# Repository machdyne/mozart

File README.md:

# Mozart Motherboard

Mozart is a motherboard that when paired with a [Sechzig](https://github.com/machdyne/sechzig) compute module can function as a computer.

This repo contains schematics, PCB layouts, pinouts and documentation.

Find more information on the [Mozart product page](https://machdyne.com/product/mozart-motherboard/).

## Using Mozart

Mozart requires a Sechzig module to power on. **When inserting a Sechzig module, make sure that pin 2 on Mozart and pin 2 on the module are both on the same side.**

## Firmware

Mozart has a JTAG and USB CDC interface that are both accessible on the USB-C port. These interfaces are provided by a [fork of pico-dirtyJtag](https://github.com/machdyne/mozart/tree/main/firmware). You can update the RP2040 firmware by holding down the BOOT button and then applying power.

To build the firmware from source:

```
$ cd firmware/pico-dirtyJtag
$ mkdir build
# if your Mozart has Zetta flash:
$ cmake ..
# or if your Mozart has Adesto flash:
$ cmake .. -DPICO_DEFAULT_BOOT_STAGE2_FILE=/your-pico-sdk-directory/pico-sdk/src/rp2_common/boot_stage2/boot2_generic_03h.S
# then
$ make
```

## Programming

Program the configuration SRAM of a Sechzig module:

```
sudo openFPGALoader -c dirtyJtag image.bit
```

Program the configuration flash on a Sechzig ML module:

```
sudo openFPGALoader -f -c dirtyJtag image.bit
```

Program the configuration flash on a Sechzig MX1 module:

```
sudo openFPGALoader -c dirtyJtag -f image.bit --fpga-part xc7a35tftg256
```

## Linux

See the [Kakao Linux](https://github.com/machdyne/kakao) repo for the latest instructions.

## Pinouts

### LVDS Port

Mozart has an experimental SATA-style LVDS port. SATA is not supported.

| Pin | Signal |
| --- | ------ |
| 1 | GND |
| 2 | DS2\_P |
| 3 | DS2\_N |
| 4 | GND |
| 5 | DS1\_P |
| 6 | DS1\_N |
| 7 | GND |

### Audio Jack

Mozart has line-level audio output via a 3.5mm jack.

| Pin | Signal |
| --- | ------ |
| S | GND |
| R2 | NC |
| R1 | AUDIO\_R |
| T | AUDIO\_L |

### Audio Amp Port

Mozart has a socket for an optional audio amplifier, so that speakers
can be connected to the DAC output.

| Pin | Signal |
| --- | ------ |
| 1 | 5V0 |
| 2 | AUDIO\_L |
| 3 | AUDIO\_R |
| 4 | GND |

### DDMI Port

See the [DDMI repo](https://github.com/machdyne/ddmi) for details.

## Funding

This project was partially funded through the NGI0 Entrust Fund, a fund established by NLnet with financial support from the European Commission's Next Generation Internet programme.

## License

This project is released under the [CERN-OHL-P](LICENSE.txt) license.

Note: You can use these designs for commercial purposes but we ask that instead of producing exact clones, that you either replace our trademarks and logos with your own or add your own next to ours.

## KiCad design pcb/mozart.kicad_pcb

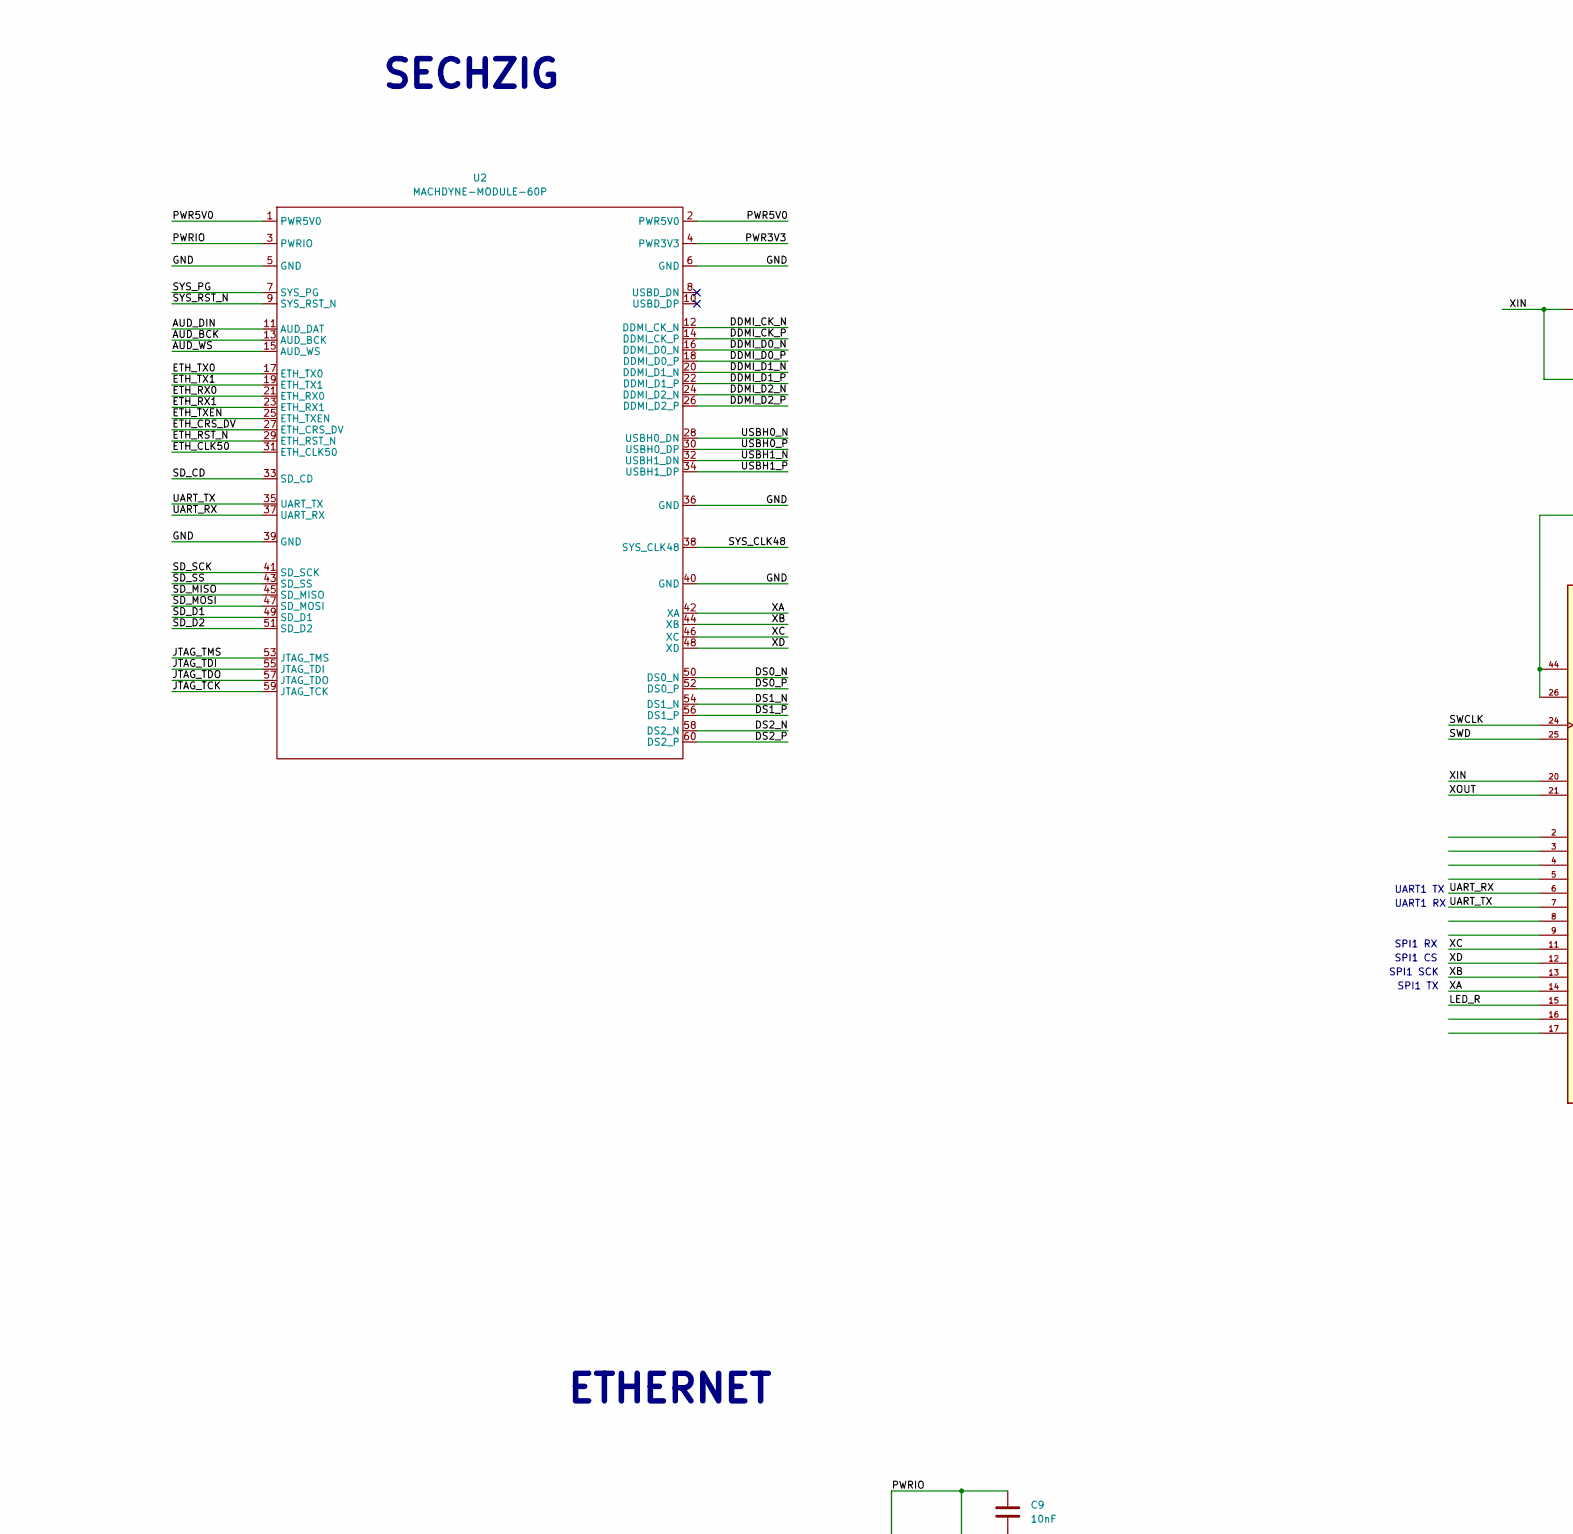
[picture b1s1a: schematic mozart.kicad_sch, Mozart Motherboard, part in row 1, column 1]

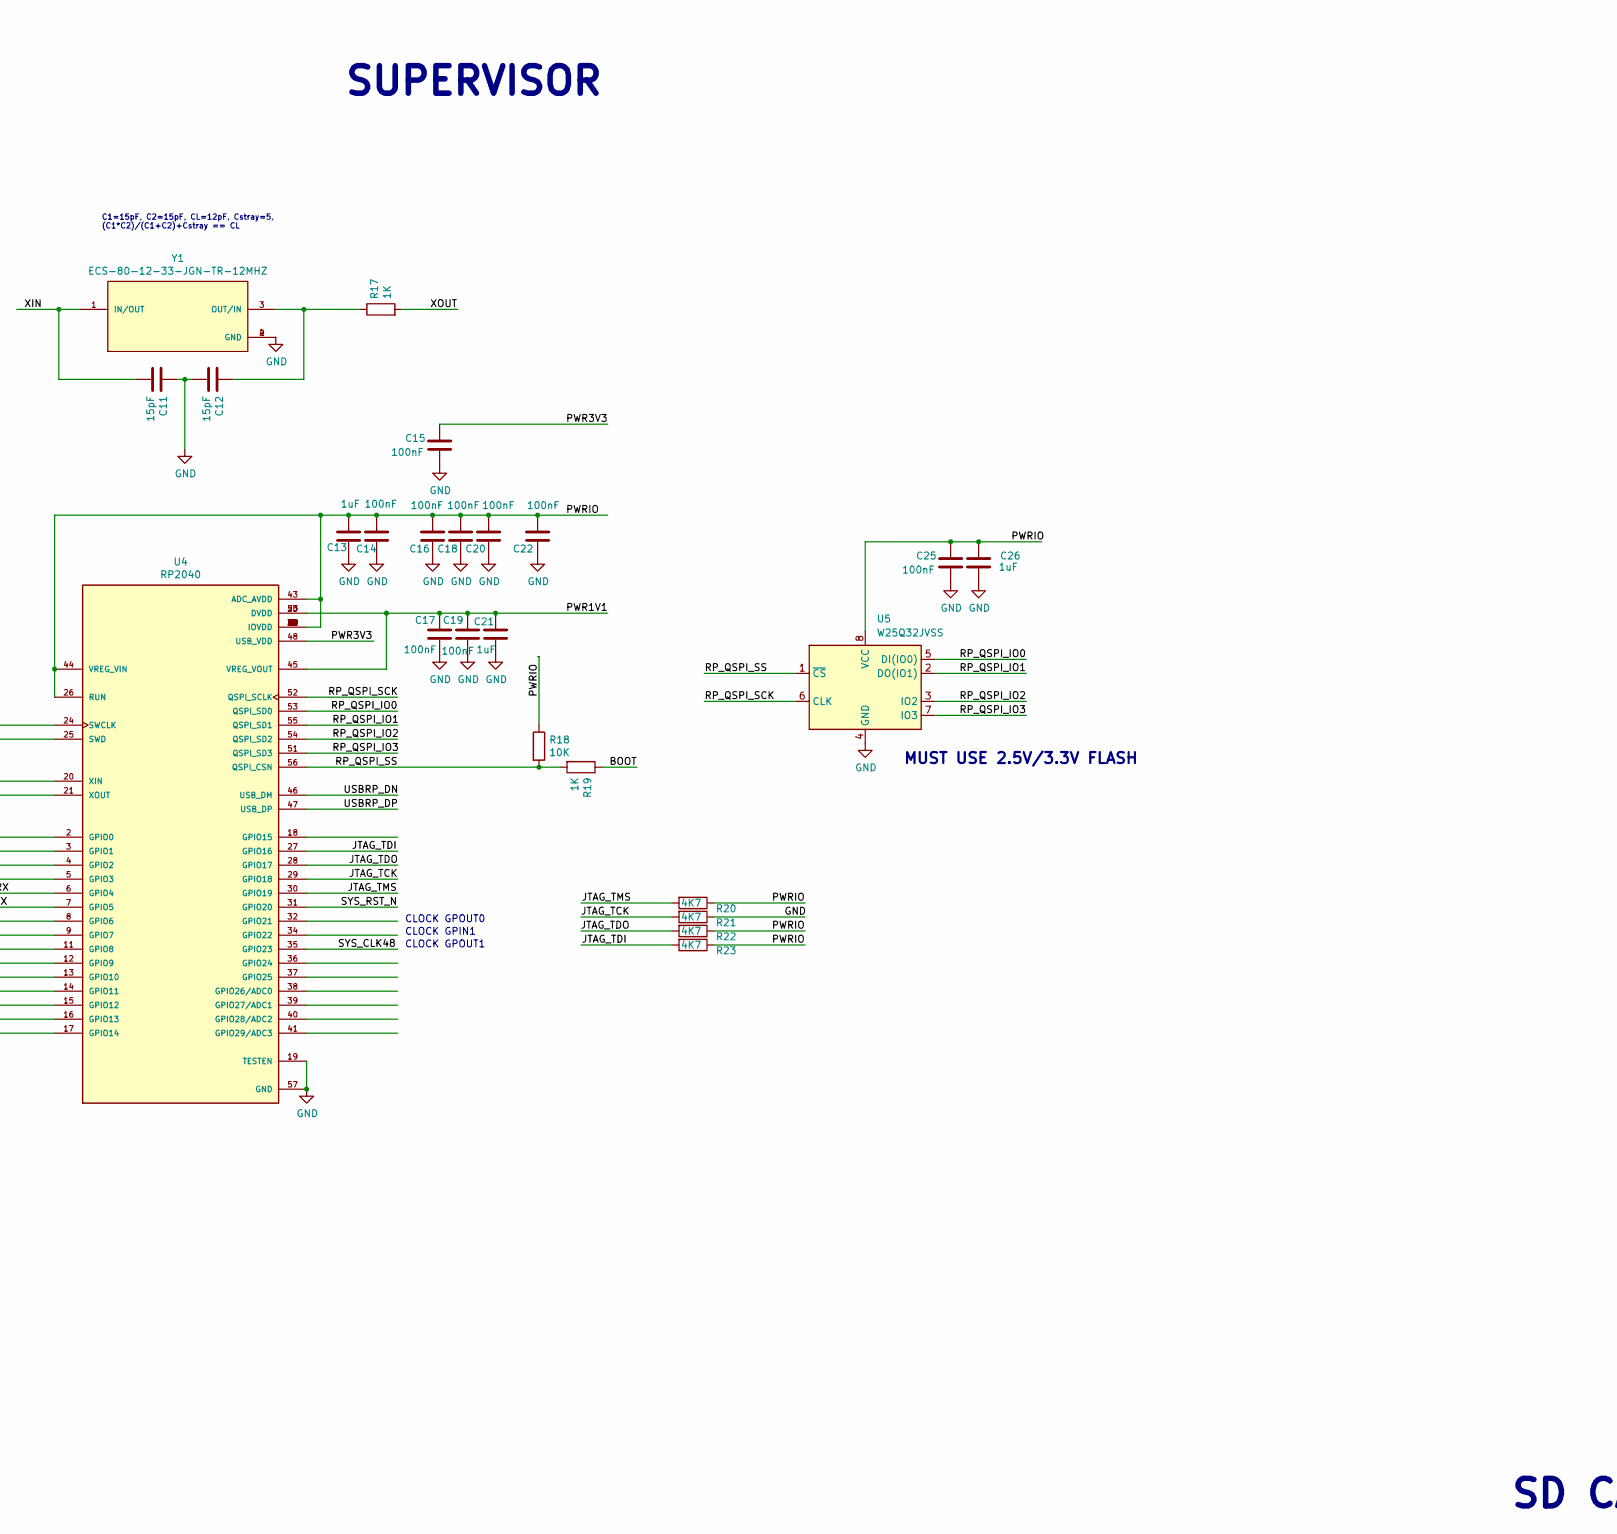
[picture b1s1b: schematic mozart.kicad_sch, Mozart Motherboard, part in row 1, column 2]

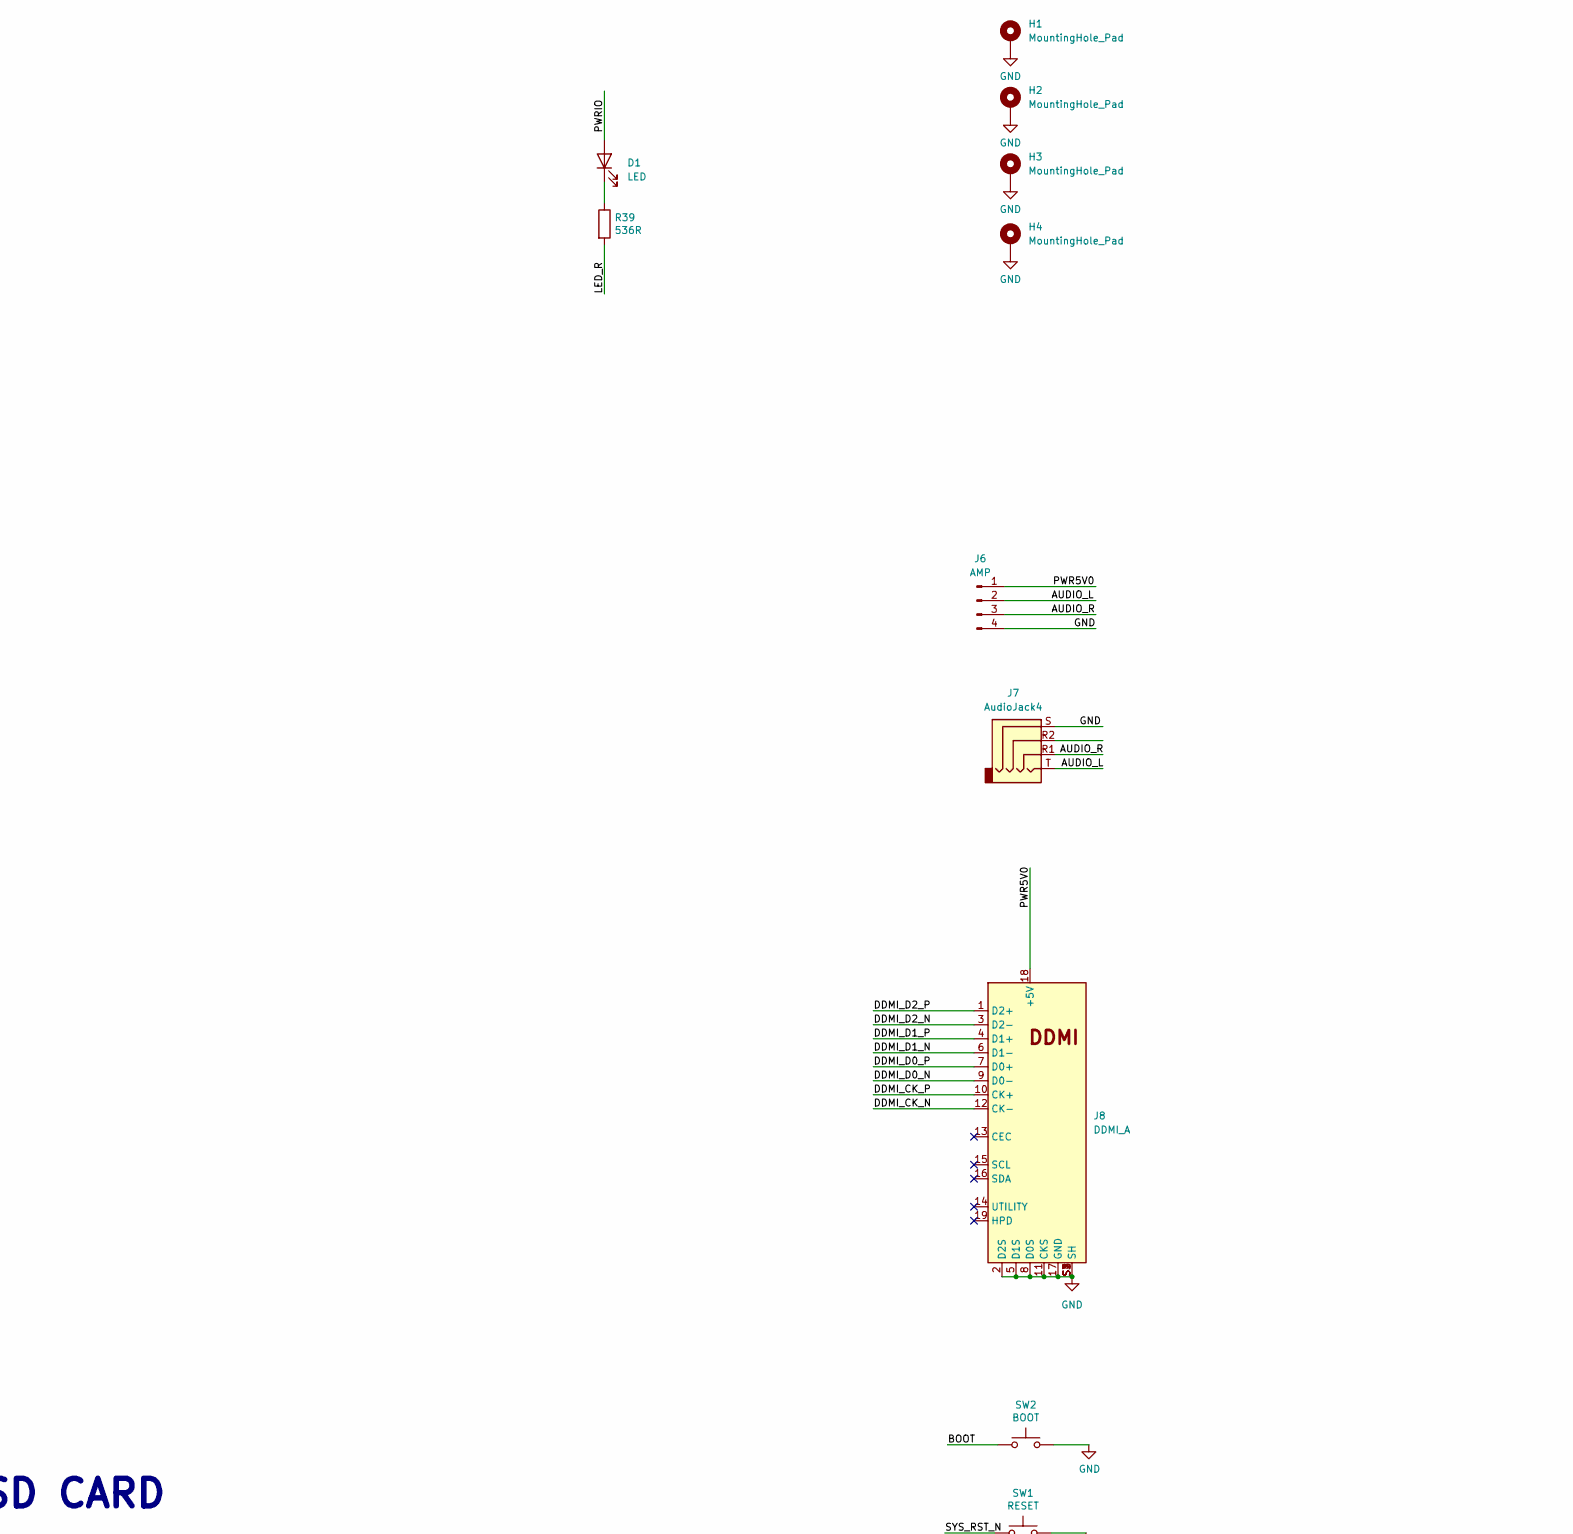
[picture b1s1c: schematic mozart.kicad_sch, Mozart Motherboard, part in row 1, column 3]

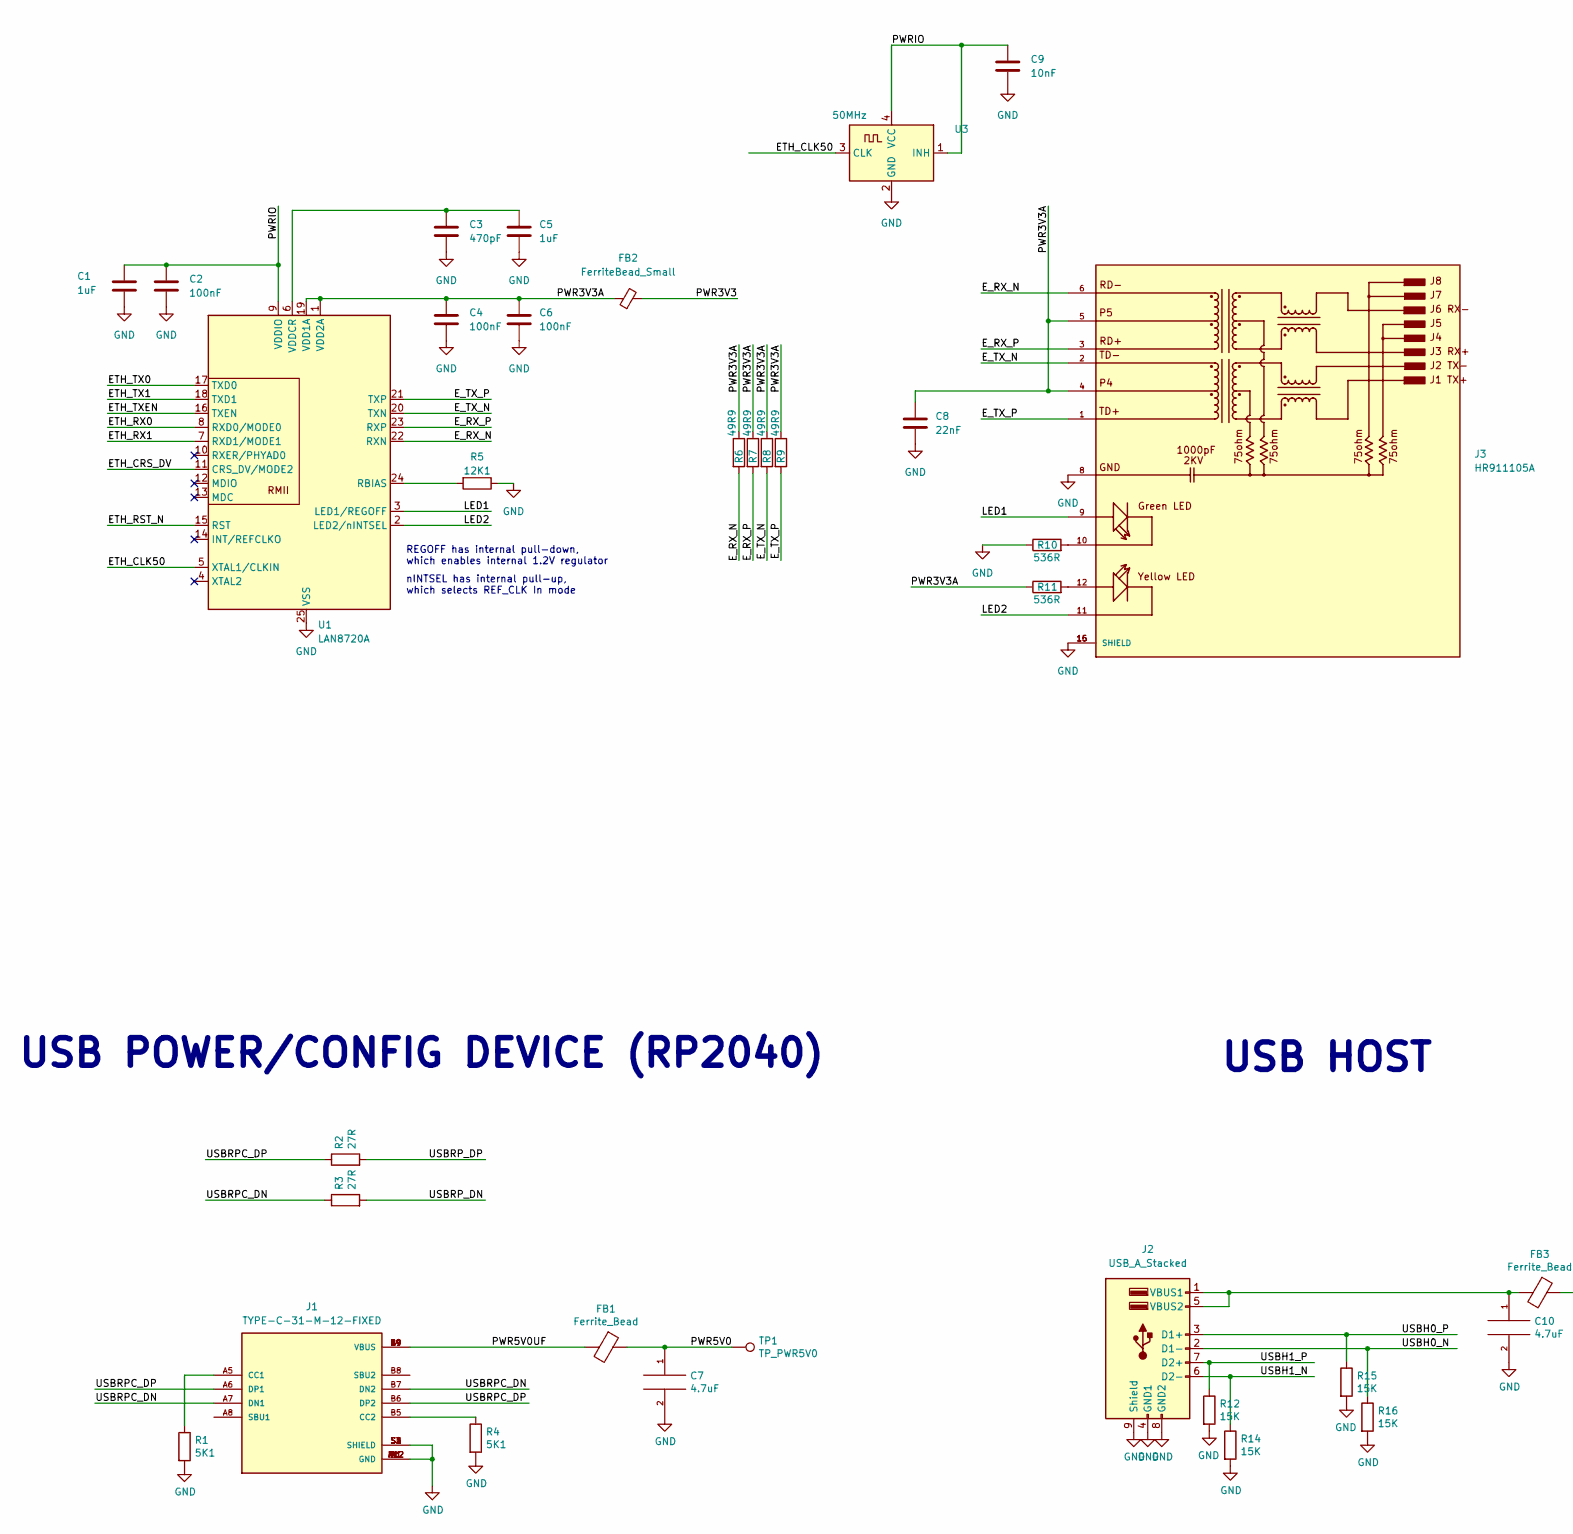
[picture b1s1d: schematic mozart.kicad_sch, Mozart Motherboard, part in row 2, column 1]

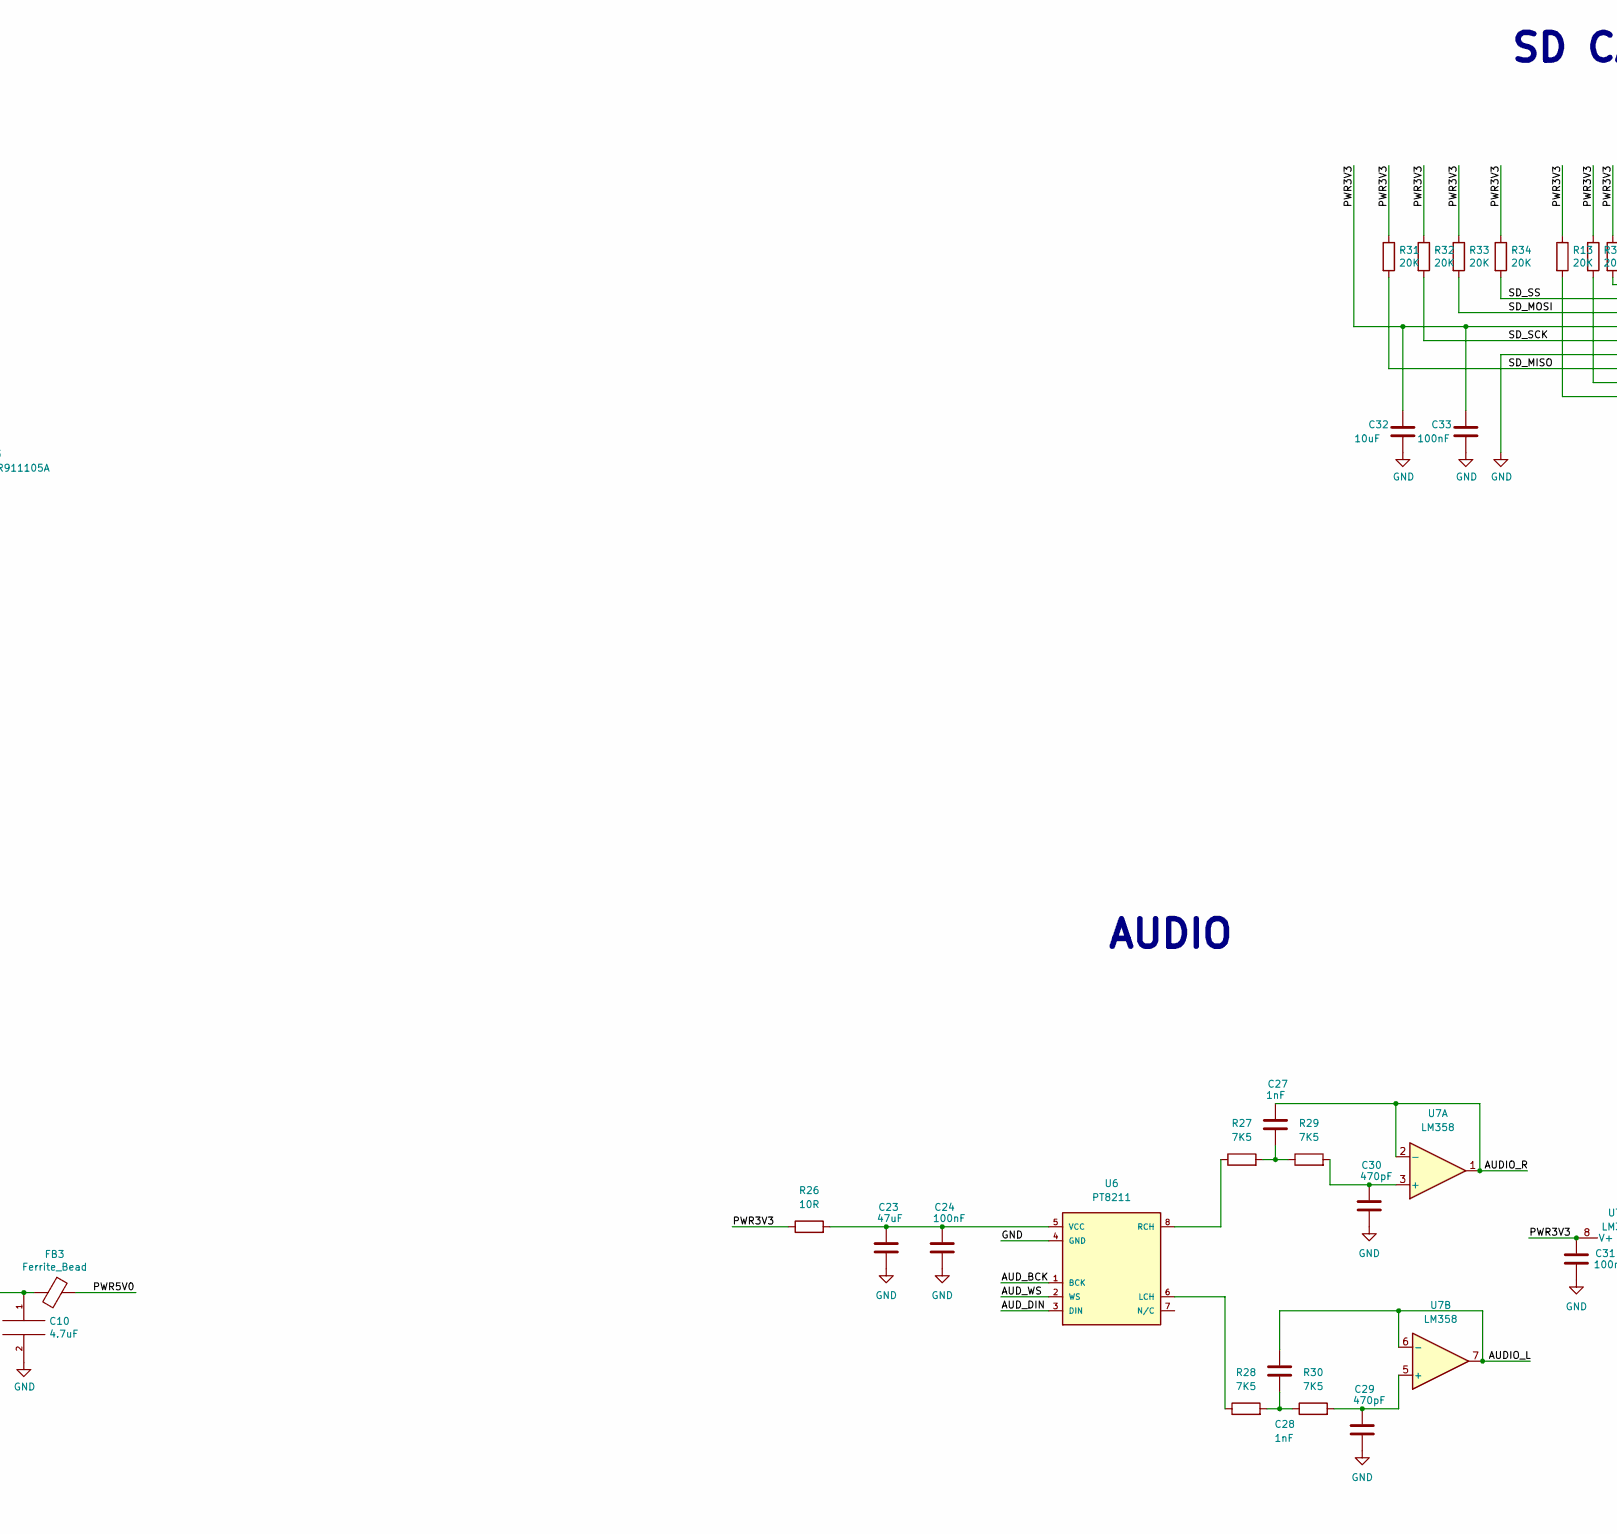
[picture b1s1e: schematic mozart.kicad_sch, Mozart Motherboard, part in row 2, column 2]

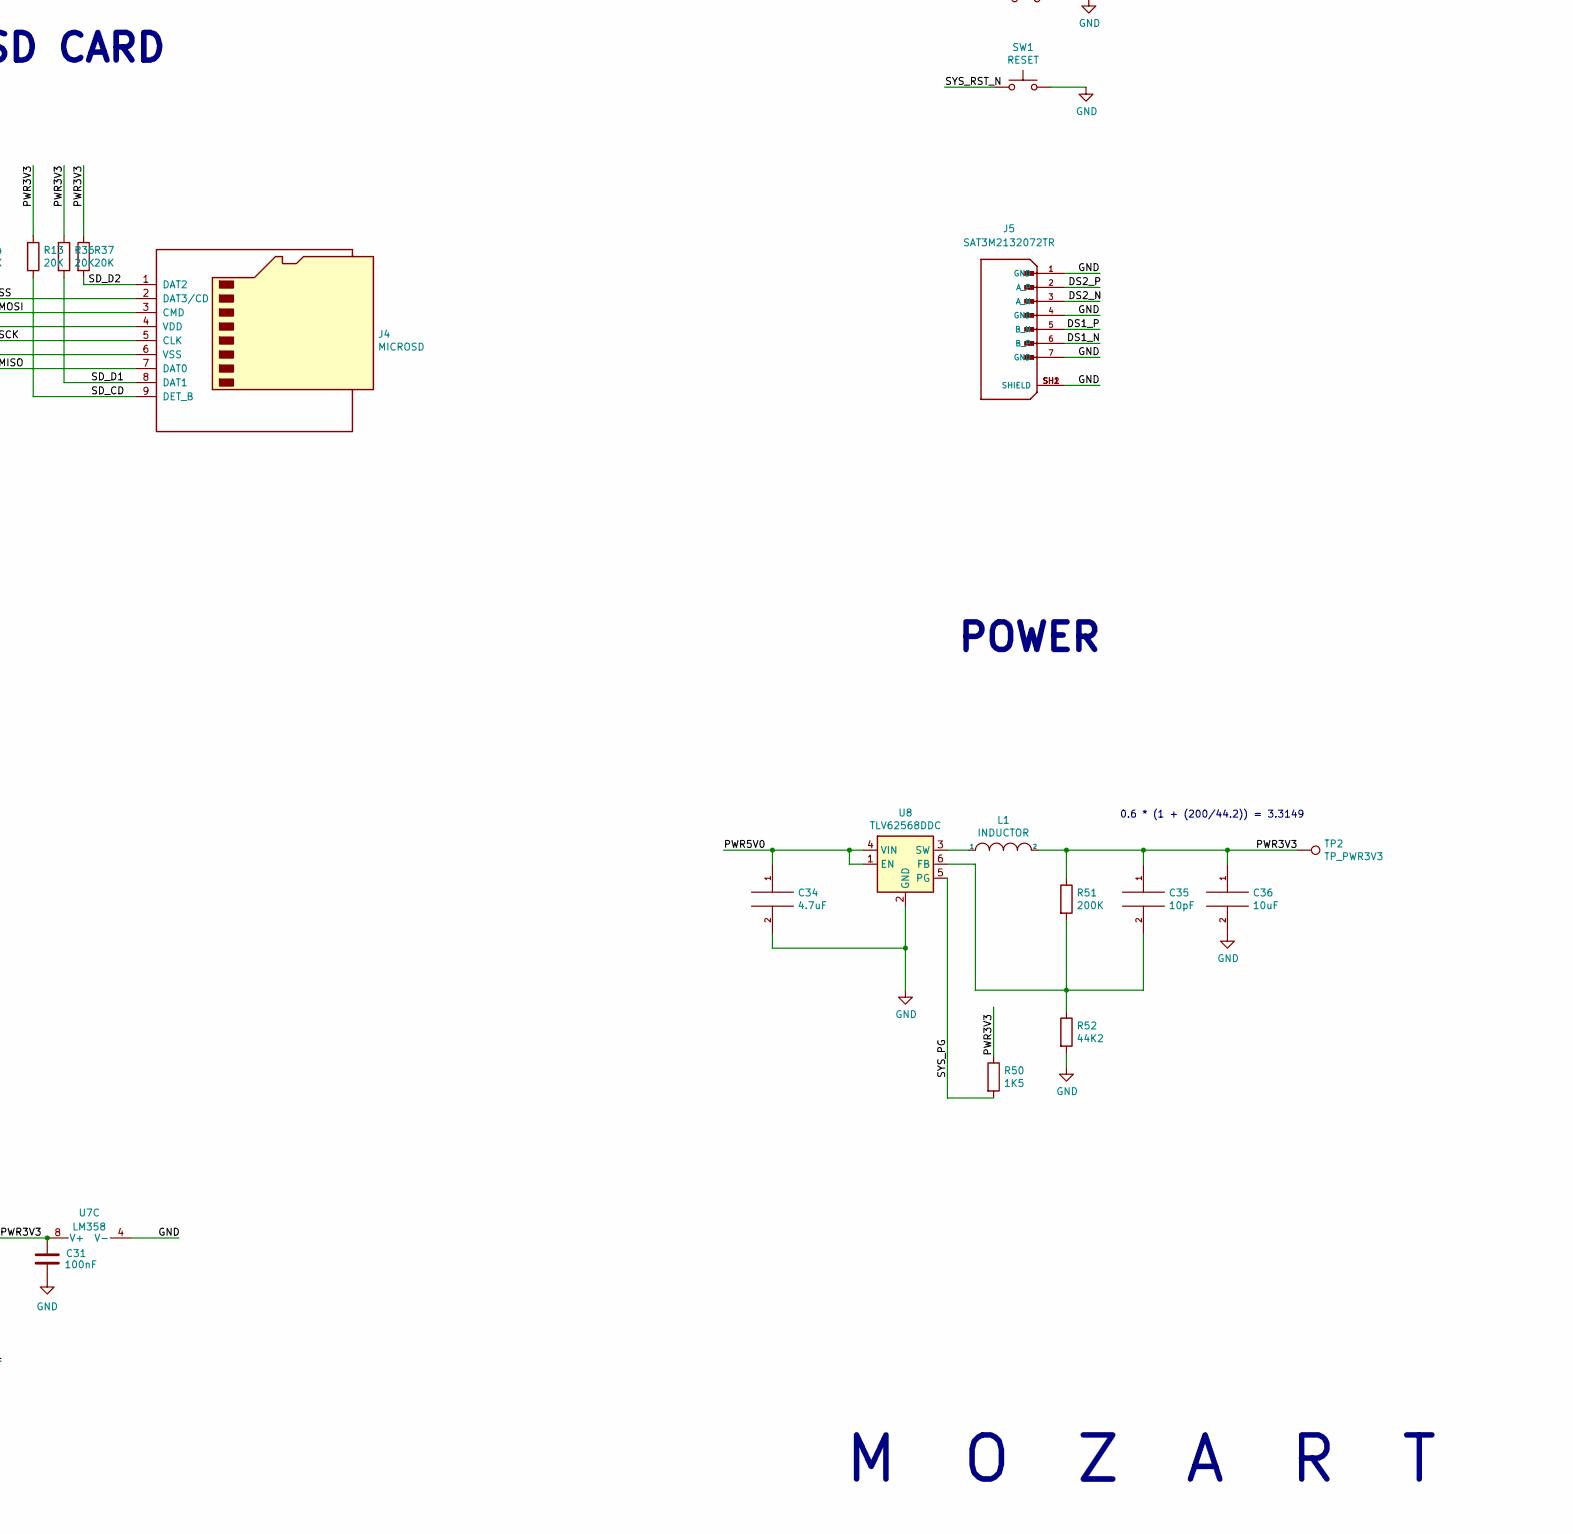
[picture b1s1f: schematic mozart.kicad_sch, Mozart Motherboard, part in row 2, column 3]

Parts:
C1, C5, C13, C21, C26: 1uF; C_0603_1608Metric
C2, C4, C6, C14, C15, C16, C17, C18, C19, C20, C22, C24, C25, C31: 100nF; C_0603_1608Metric
C3, C29, C30: 470pF; C_0603_1608Metric
C7, C10, C34: 4.7uF; C_0603_1608Metric
C8: 22nF; C_0603_1608Metric
C9: 10nF; C_0603_1608Metric
C11, C12: 15pF; C_0603_1608Metric
C23: 47uF; C_0603_1608Metric
C27, C28: 1nF; C_0603_1608Metric
C32: 10uF; R_0603_1608Metric
C33: 100nF; R_0603_1608Metric
C35: 10pF; C_0603_1608Metric
C36: 10uF; C_0603_1608Metric
D1: LED; LED_1206_3216Metric
FB1, FB3: Ferrite_Bead; R_0603_1608Metric
FB2: FerriteBead_Small; R_0603_1608Metric
H1, H2, H3, H4: MountingHole_Pad; MountingHole_3.2mm_M3_Pad
J1: TYPE-C-31-M-12-FIXED; USB_C_Receptacle_HRO_TYPE-C-31-M-12-BIG-PADS; PARTREV A
J2: USB_A_Stacked; USB_A_Wuerth_61400826021_Horizontal_Stacked
J3: HR911105A; HANRUN_HR911105A; PARTREV A
J4: MICROSD; SDCARD
J5: SAT3M2132072TR; AMPHENOL_SAT3M2132072TR; PARTREV 1
J6: AMP; PinSocket_1x04_P2.54mm_Vertical
J7: AudioJack4; Jack_3.5mm_PJ320D_Horizontal
J8: DDMI_A; HDMI_TE_1827059-3-FIXED
L1: INDUCTOR; L_0805_2012Metric
R1, R4: 5K1; R_0603_1608Metric
R2, R3: 27R; R_0603_1608Metric
R5: 12K1; R_0603_1608Metric
R6, R7, R8, R9: 49R9; R_0603_1608Metric
R10, R11, R39: 536R; R_0603_1608Metric
R12, R14, R15, R16: 15K; R_0603_1608Metric
R13, R31, R32, R33, R34, R36, R37: 20K; R_0603_1608Metric
R17, R19: 1K; R_0603_1608Metric
R18: 10K; R_0603_1608Metric
R20, R21, R22, R23: 4K7; R_0603_1608Metric
R26: 10R; R_0603_1608Metric
R27, R28, R29, R30: 7K5; R_0603_1608Metric
R50: 1K5; R_0603_1608Metric
R51: 200K; R_0603_1608Metric
R52: 44K2; R_0603_1608Metric
SW1: RESET; SW_Tactile_SPST_Angled_PTS645Vx39-2LFS
SW2: BOOT; SW_Tactile_SPST_Angled_PTS645Vx39-2LFS
TP1: TP_PWR5V0; TestPoint_THTPad_D1.0mm_Drill0.5mm
TP2: TP_PWR3V3; TestPoint_THTPad_D1.0mm_Drill0.5mm
U1: LAN8720A; QFN-24-1EP_4x4mm_P0.5mm_EP2.6x2.6mm
U2: MACHDYNE-MODULE-60P; MACHDYNE_EDGE_SOCKET_60P
U3: 50MHz; Oscillator_SMD_Kyocera_KC2520Z-4Pin_2.5x2.0mm
U4: RP2040; RP2040-QFN-56-OFFICIAL; PARTREV 1.6.1
U5: W25Q32JVSS; SOIC-8_3.9x4.9mm_P1.27mm
U6: PT8211; SOP-8_3.9x4.9mm_P1.27mm
U7: LM358
U8: TLV62568DDC; SOT-23-6
Y1: ECS-80-12-33-JGN-TR-12MHZ; XTAL_ECS-240-8-33-AGN-TR

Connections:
/AUDIO_L: C28.1, J6.2, J7.T, U7.6 (-), U7.7
/AUDIO_R: C27.1, J6.3, J7.R1, U7.1, U7.2 (-)
/AUD_BCK: U2.13 (AUD_BCK), U6.1 (BCK)
/AUD_DIN: U2.11 (AUD_DAT), U6.3 (DIN)
/AUD_WS: U2.15 (AUD_WS), U6.2 (WS)
/BOOT: R19.1, SW2.1
/DDMI_CK_N: J8.12 (CK-), U2.12 (DDMI_CK_N)
/DDMI_CK_P: J8.10 (CK+), U2.14 (DDMI_CK_P)
/DDMI_D0_N: J8.9 (D0-), U2.16 (DDMI_D0_N)
/DDMI_D0_P: J8.7 (D0+), U2.18 (DDMI_D0_P)
/DDMI_D1_N: J8.6 (D1-), U2.20 (DDMI_D1_N)
/DDMI_D1_P: J8.4 (D1+), U2.22 (DDMI_D1_P)
/DDMI_D2_N: J8.3 (D2-), U2.24 (DDMI_D2_N)
/DDMI_D2_P: J8.1 (D2+), U2.26 (DDMI_D2_P)
/DS0_N: U2.50 (DS0_N)
/DS0_P: U2.52 (DS0_P)
/DS1_N: J5.6 (B_P), U2.54 (DS1_N)
/DS1_P: J5.5 (B_N), U2.56 (DS1_P)
/DS2_N: J5.3 (A_N), U2.58 (DS2_N)
/DS2_P: J5.2 (A_P), U2.60 (DS2_P)
/ETH_CLK50: U1.5 (XTAL1/CLKIN), U2.31 (ETH_CLK50), U3.3 (CLK)
/ETH_CRS_DV: U1.11 (CRS_DV/MODE2), U2.27 (ETH_CRS_DV)
/ETH_RST_N: U1.15 (RST), U2.29 (ETH_RST_N)
/ETH_RX0: U1.8 (RXD0/MODE0), U2.21 (ETH_RX0)
/ETH_RX1: U1.7 (RXD1/MODE1), U2.23 (ETH_RX1)
/ETH_TX0: U1.17 (TXD0), U2.17 (ETH_TX0)
/ETH_TX1: U1.18 (TXD1), U2.19 (ETH_TX1)
/ETH_TXEN: U1.16 (TXEN), U2.25 (ETH_TXEN)
/E_RX_N: J3.6, R6.2, U1.22 (RXN)
/E_RX_P: J3.3, R7.2, U1.23 (RXP)
/E_TX_N: J3.2, R8.2, U1.20 (TXN)
/E_TX_P: J3.1, R9.2, U1.21 (TXP)
/JTAG_TCK: R21.2, U2.59 (JTAG_TCK), U4.29 (GPIO18)
/JTAG_TDI: R23.2, U2.55 (JTAG_TDI), U4.27 (GPIO16)
/JTAG_TDO: R22.2, U2.57 (JTAG_TDO), U4.28 (GPIO17)
/JTAG_TMS: R20.2, U2.53 (JTAG_TMS), U4.30 (GPIO19)
/LED1: J3.9, U1.3 (LED1/REGOFF)
/LED2: J3.11, U1.2 (LED2/nINTSEL)
/LED_R: R39.2, U4.15 (GPIO12)
/PWR1V1: C17.1, C19.1, C21.1, U4.23 (DVDD), U4.45 (VREG_VOUT), U4.50 (DVDD)
/PWR3V3: C15.1, C31.1, C32.1, C33.1, C35.1, C36.1, FB2.2, J4.4 (VDD), L1.2, R13.1, R26.1, R31.1, R32.1, R33.1, R34.1, R36.1, R37.1, R50.1, R51.1, TP2.1, U2.4 (PWR3V3), U4.48 (USB_VDD), U7.8 (V+)
/PWR3V3A: C4.1, C6.1, C8.1, FB2.1, J3.4, J3.5, R6.1, R7.1, R8.1, R9.1, R11.1, U1.1 (VDD2A), U1.19 (VDD1A)
/PWR5V0: C7.1, C34.1, FB1.1, FB3.1, J6.1, J8.18 (+5V), TP1.1, U2.1 (PWR5V0), U2.2 (PWR5V0), U8.1 (EN), U8.4 (VIN)
/PWR5V0UF: FB1.2, J1.A4 (VBUS), J1.A9 (VBUS), J1.B4 (VBUS), J1.B9 (VBUS)
/PWRIO: C1.1, C2.1, C9.1, C13.1, C14.1, C16.1, C18.1, C20.1, C22.1, C25.1, C26.1, D1.2 (A), R18.1, R20.1, R22.1, R23.1, U1.9 (VDDIO), U2.3 (PWRIO), U3.1 (INH), U3.4 (VCC), U4.1 (IOVDD), U4.10 (IOVDD), U4.22 (IOVDD), U4.26 (RUN), U4.33 (IOVDD), U4.42 (IOVDD), U4.43 (ADC_AVDD), U4.44 (VREG_VIN), U4.49 (IOVDD), U5.8 (VCC)
/RP_QSPI_IO0: U4.53 (QSPI_SD0), U5.5 (DI(IO0))
/RP_QSPI_IO1: U4.55 (QSPI_SD1), U5.2 (DO(IO1))
/RP_QSPI_IO2: U4.54 (QSPI_SD2), U5.3 (IO2)
/RP_QSPI_IO3: U4.51 (QSPI_SD3), U5.7 (IO3)
/RP_QSPI_SCK: U4.52 (QSPI_SCLK), U5.6 (CLK)
/RP_QSPI_SS: R18.2, R19.2, U4.56 (QSPI_CSN), U5.1 (~CS)
/SD_CD: J4.9 (DET_B), R13.2, U2.33 (SD_CD)
/SD_D1: J4.8 (DAT1), R36.2, U2.49 (SD_D1)
/SD_D2: J4.1 (DAT2), R37.2, U2.51 (SD_D2)
/SD_MISO: J4.7 (DAT0), R31.2, U2.45 (SD_MISO)
/SD_MOSI: J4.3 (CMD), R33.2, U2.47 (SD_MOSI)
/SD_SCK: J4.5 (CLK), R32.2, U2.41 (SD_SCK)
/SD_SS: J4.2 (DAT3/CD), R34.2, U2.43 (SD_SS)
/SWCLK: U4.24 (SWCLK)
/SWD: U4.25 (SWD)
/SYS_CLK48: U2.38 (SYS_CLK48), U4.35 (GPIO23)
/SYS_PG: R50.2, U2.7 (SYS_PG), U8.5 (PG)
/SYS_RST_N: SW1.1, U2.9 (SYS_RST_N), U4.31 (GPIO20)
/UART_RX: U2.37 (UART_RX), U4.6 (GPIO4)
/UART_TX: U2.35 (UART_TX), U4.7 (GPIO5)
/USBH0_N: J2.2 (D1-), R16.1, U2.28 (USBH0_DN)
/USBH0_P: J2.3 (D1+), R15.1, U2.30 (USBH0_DP)
/USBH1_N: J2.6 (D2-), R14.1, U2.32 (USBH1_DN)
/USBH1_P: J2.7 (D2+), R12.1, U2.34 (USBH1_DP)
/USBRPC_DN: J1.A7 (DN1), J1.B7 (DN2), R3.1
/USBRPC_DP: J1.A6 (DP1), J1.B6 (DP2), R2.1
/USBRP_DN: R3.2, U4.46 (USB_DM)
/USBRP_DP: R2.2, U4.47 (USB_DP)
/XA: U2.42 (XA), U4.14 (GPIO11)
/XB: U2.44 (XB), U4.13 (GPIO10)
/XC: U2.46 (XC), U4.11 (GPIO8)
/XD: U2.48 (XD), U4.12 (GPIO9)
/XIN: C11.2, U4.20 (XIN), Y1.1 (IN/OUT)
/XOUT: R17.2, U4.21 (XOUT)
GND: C1.2, C2.2, C3.2, C4.2, C5.2, C6.2, C7.2, C8.2, C9.2, C10.2, C11.1, C12.2, C13.2, C14.2, C15.2, C16.2, C17.2, C18.2, C19.2, C20.2, C21.2, C22.2, C23.2, C24.2, C25.2, C26.2, C29.2, C30.2, C31.2, C32.2, C33.2, C34.2, C36.2, H1.1, H2.1, H3.1, H4.1, J1.A1 (GND), J1.A12 (GND), J1.B1 (GND), J1.B12 (GND), J1.S1 (SHIELD), J1.S2 (SHIELD), J1.S3 (SHIELD), J1.S4 (SHIELD), J2.4 (GND1), J2.8 (GND2), J2.9 (Shield), J3.8, J3.15 (SHIELD), J3.16 (SHIELD), J4.6 (VSS), J5.1 (GND), J5.4 (GND), J5.7 (GND), J5.SH1 (SHIELD), J5.SH2 (SHIELD), J6.4, J7.S, J8.2 (D2S), J8.5 (D1S), J8.8 (D0S), J8.11 (CKS), J8.17 (GND), J8.S1 (SH), J8.S2 (SH), J8.S3 (SH), J8.S4 (SH), R1.2, R4.2, R5.1, R10.1, R12.2, R14.2, R15.2, R16.2, R21.1, R52.2, SW1.2, SW2.2, U1.25 (VSS), U2.5 (GND), U2.6 (GND), U2.36 (GND), U2.39 (GND), U2.40 (GND), U3.2 (GND), U4.19 (TESTEN), U4.57 (GND), U5.4 (GND), U6.4 (GND), U7.4 (V-), U8.2 (GND), Y1.2 (GND), Y1.4 (GND)
unnamed: C3.1, C5.1, U1.6 (VDDCR)
unnamed: C10.1, FB3.2, J2.1 (VBUS1), J2.5 (VBUS2)
unnamed: C12.1, R17.1, Y1.3 (OUT/IN)
unnamed: C23.1, C24.1, R26.2, U6.5 (VCC)
unnamed: C27.2, R27.2, R29.1
unnamed: C28.2, R28.2, R30.1
unnamed: C29.1, R30.2, U7.5 (+)
unnamed: C30.1, R29.2, U7.3 (+)
unnamed: C35.2, R51.2, R52.1, U8.6 (FB)
unnamed: D1.1 (K), R39.1
unnamed: J1.A5 (CC1), R1.1
unnamed: J1.B5 (CC2), R4.1
unnamed: J3.10, R10.2
unnamed: J3.12, R11.2
unnamed: L1.1, U8.3 (SW)
unnamed: R5.2, U1.24 (RBIAS)
unnamed: R27.1, U6.8 (RCH)
unnamed: R28.1, U6.6 (LCH)

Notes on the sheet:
CLOCK GPOUT1
M O Z A R T
nINTSEL has internal pull-up, which selects REF_CLK In mode
0.6 * (1 + (200/44.2)) = 3.3149
SD CARD
SPI1 CS
MUST USE 2.5V/3.3V FLASH
C1=15pF, C2=15pF, CL=12pF, Cstray=5, (C1*C2)/(C1+C2)+Cstray == CL
UART1 TX
REGOFF has internal pull-down, which enables internal 1.2V regulator
POWER
SECHZIG
SPI1 RX
SPI1 TX
ETHERNET
CLOCK GPIN1
USB POWER/CONFIG DEVICE (RP2040)
CLOCK GPOUT0
SUPERVISOR
AUDIO
USB HOST
SPI1 SCK
UART1 RX

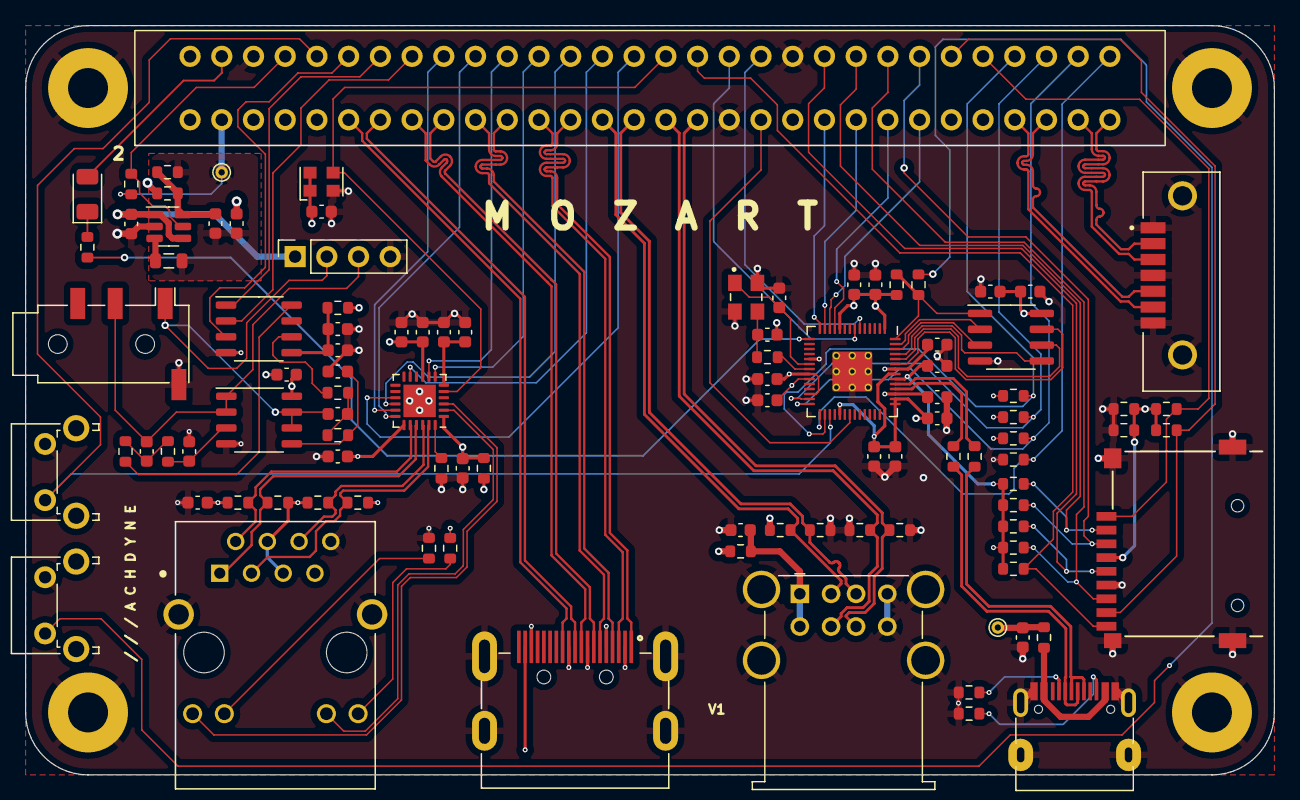
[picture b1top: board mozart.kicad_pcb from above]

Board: 4 copper layers, 100.0 x 60.0 mm, 104 parts (0 on the bottom side), 94 nets.

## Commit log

2023-11-15 change rp2040 bootloader
2023-12-04 add preliminary case design
2023-12-07 update images
2023-12-07 update image
2023-12-09 add dual core bitstream
2023-12-15 case improvements
2023-12-15 update case notes
2023-12-17 update case
2024-01-25 add ml2 images
2024-03-10 add box case
2024-03-17 add mx1 images
2024-03-19 update license
2024-05-12 add ml1_v2 image
2024-05-12 update box case
2024-06-07 add generic firmware
2024-07-25 add mx2
2024-07-25 use spi1x for configuration
2024-07-26 add mono bitstreams
2024-10-03 update bitstreams
2024-11-03 add initial ml3 images

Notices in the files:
pcb/mozart.kicad_sch:
Copyright © 2023 Lone Dynamics Corporation
